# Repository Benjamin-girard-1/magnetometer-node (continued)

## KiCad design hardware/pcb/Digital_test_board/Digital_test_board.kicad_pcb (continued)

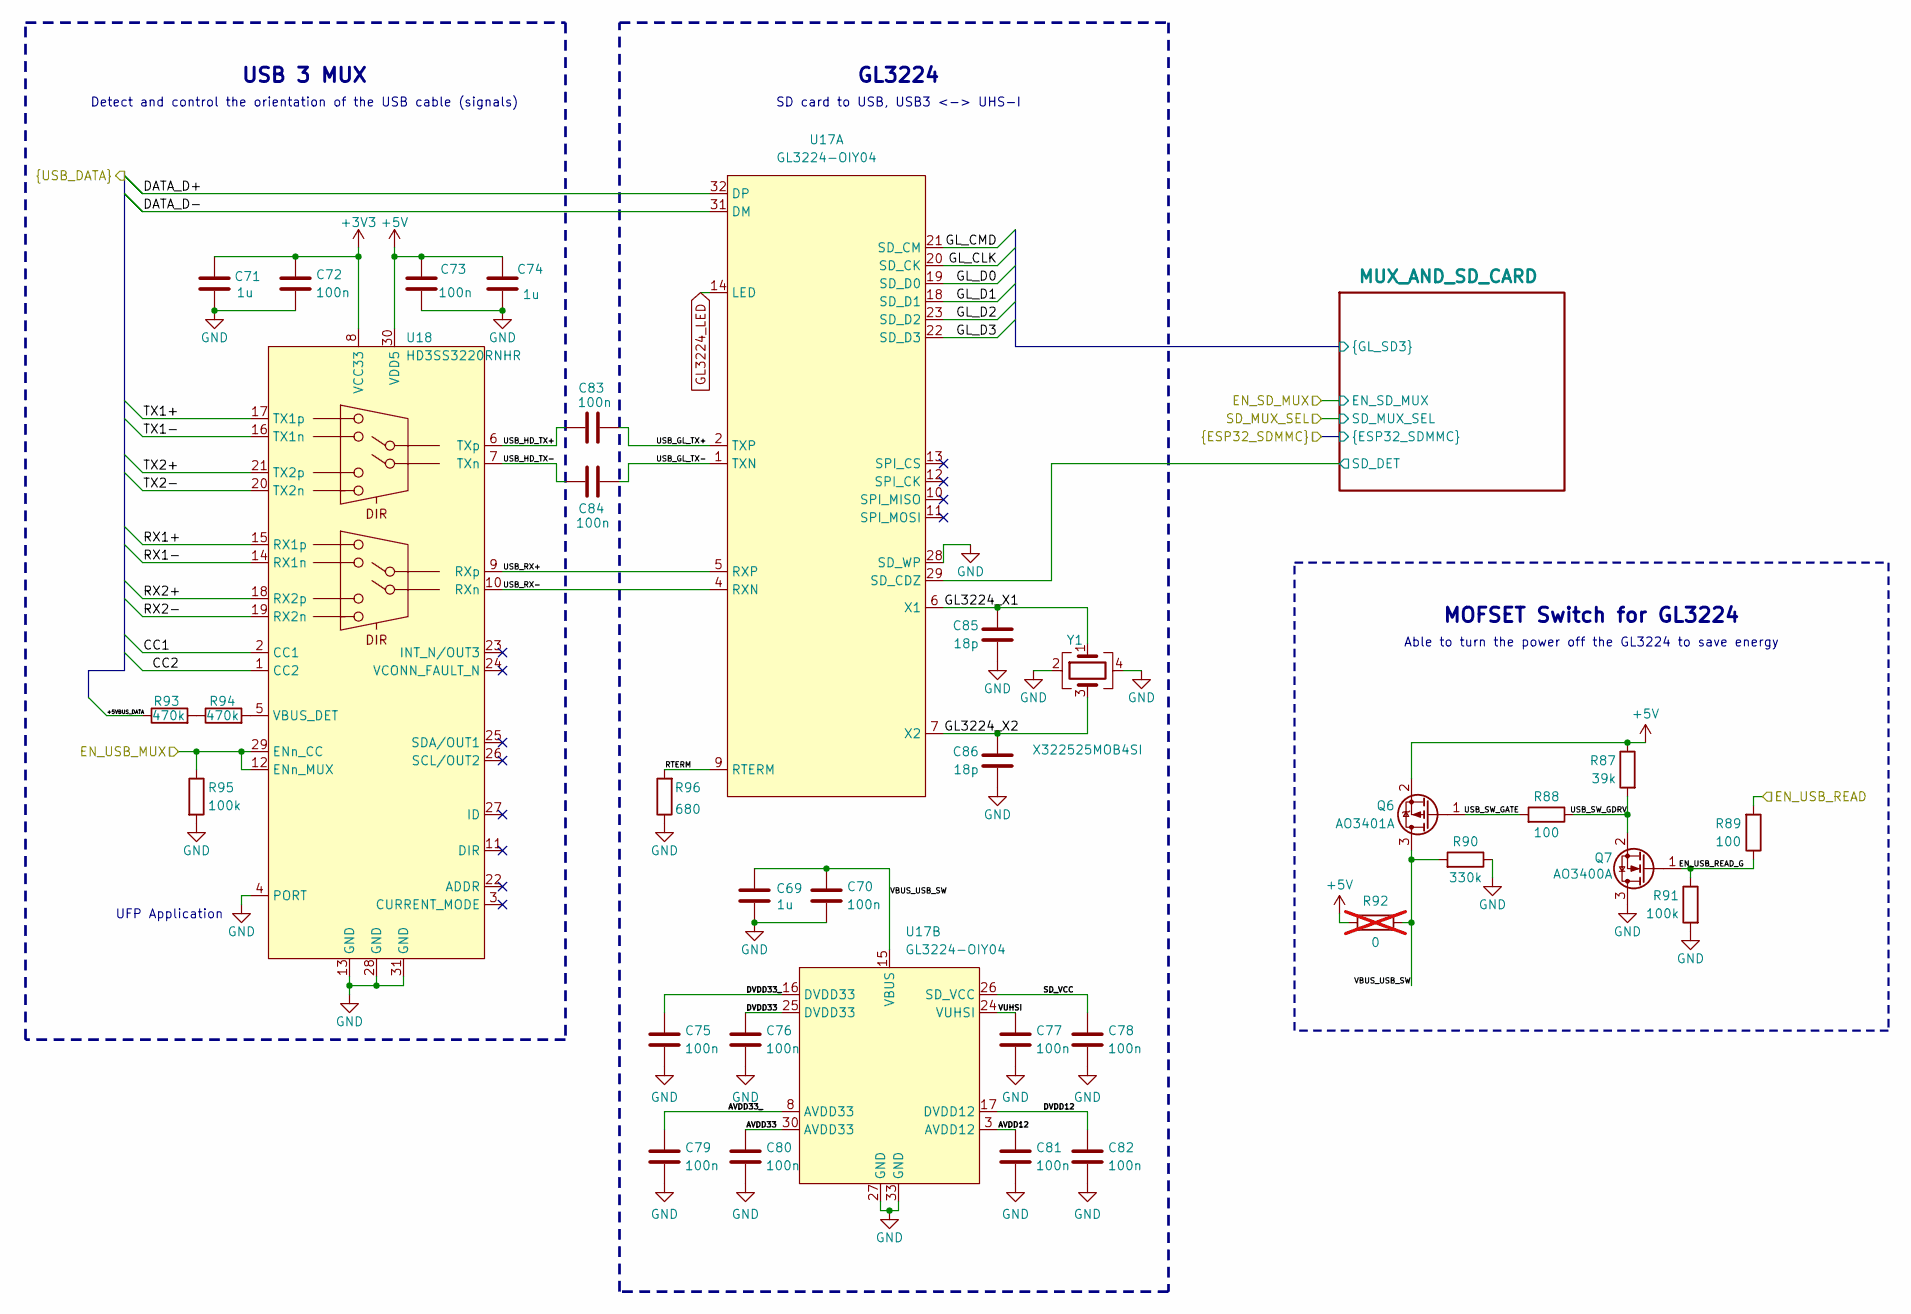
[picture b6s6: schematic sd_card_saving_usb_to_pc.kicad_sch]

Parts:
C69, C71, C74: 1u; C_0805_2012Metric; LCSC C28323
C70, C72, C73, C75, C76, C77, C78, C79, C80, C81, C82, C83, C84: 100n; C_0603_1608Metric; LCSC C14663
C85, C86: 18p; C_0603_1608Metric; LCSC C1647
Q6: AO3401A; SOT-23; LCSC C15127
Q7: AO3400A; SOT-23; LCSC C20917
R87: 39k; R_0603_1608Metric; LCSC C23153
R88, R89: 100; R_0603_1608Metric; LCSC C22775
R90: 330k; R_0603_1608Metric; LCSC C23137
R91, R95: 100k; R_0603_1608Metric; LCSC C25803
R92: 0; R_1206_3216Metric; LCSC C17888; not fitted
R93, R94: 470k; R_0603_1608Metric; LCSC C23178
R96: 680; R_0603_1608Metric; LCSC C23228
U17: GL3224-OIY04; QFN-32-1EP_5x5mm_P0.5mm_EP3.1x3.1mm; LCSC C157357
U18: HD3SS3220RNHR; Texas_RNH0030A_WQFN-30-1EP_2.5x4.5mm_P0.4mm_EP1.2x3.2mm; LCSC C165155
Y1: X322525MOB4SI; Crystal_SMD_3225-4Pin_3.2x2.5mm; LCSC C9006

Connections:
+3V3: C71.2, C72.1, U18.8 (VCC33); also elsewhere on the board
+5V: C73.1, C74.2, Q6.2 (S), R87.1, R92.2, U18.30 (VDD5); also elsewhere on the board
/DATA_SAVING/+5VBUS_DATA: R93.1; also elsewhere on the board
/DATA_SAVING/+5VBUS_DET: R94.2, U18.5 (VBUS_DET)
/DATA_SAVING/AVDD12: C81.1, U17.3 (AVDD12)
/DATA_SAVING/AVDD33: C80.1, U17.30 (AVDD33)
/DATA_SAVING/AVDD33_: C79.1, U17.8 (AVDD33)
/DATA_SAVING/CC1: U18.2 (CC1); also elsewhere on the board
/DATA_SAVING/CC2: U18.1 (CC2); also elsewhere on the board
/DATA_SAVING/DATA_D+: U17.32 (DP); also elsewhere on the board
/DATA_SAVING/DATA_D-: U17.31 (DM); also elsewhere on the board
/DATA_SAVING/DVDD12: C82.1, U17.17 (DVDD12)
/DATA_SAVING/DVDD33: C76.1, U17.25 (DVDD33)
/DATA_SAVING/DVDD33_: C75.1, U17.16 (DVDD33)
/DATA_SAVING/EN_USB_MUX: R95.1, U18.12 (ENn_MUX), U18.29 (ENn_CC); also elsewhere on the board
/DATA_SAVING/EN_USB_READ: R89.2; also elsewhere on the board
/DATA_SAVING/EN_USB_READ_G: Q7.1 (G), R89.1, R91.1
/DATA_SAVING/GL3224_X1: C85.1, U17.6 (X1), Y1.1
/DATA_SAVING/GL3224_X2: C86.1, U17.7 (X2), Y1.3
/DATA_SAVING/MUX_AND_SD_CARD/GL_CLK: U17.20 (SD_CK); also elsewhere on the board
/DATA_SAVING/MUX_AND_SD_CARD/GL_CMD: U17.21 (SD_CM); also elsewhere on the board
/DATA_SAVING/MUX_AND_SD_CARD/GL_D0: U17.19 (SD_D0); also elsewhere on the board
/DATA_SAVING/MUX_AND_SD_CARD/GL_D1: U17.18 (SD_D1); also elsewhere on the board
/DATA_SAVING/MUX_AND_SD_CARD/GL_D2: U17.23 (SD_D2); also elsewhere on the board
/DATA_SAVING/MUX_AND_SD_CARD/GL_D3: U17.22 (SD_D3); also elsewhere on the board
/DATA_SAVING/MUX_AND_SD_CARD/SD_DET: U17.29 (SD_CDZ); also elsewhere on the board
/DATA_SAVING/RTERM: R96.2, U17.9 (RTERM)
/DATA_SAVING/RX1+: U18.15 (RX1p); also elsewhere on the board
/DATA_SAVING/RX1-: U18.14 (RX1n); also elsewhere on the board
/DATA_SAVING/RX2+: U18.18 (RX2p); also elsewhere on the board
/DATA_SAVING/RX2-: U18.19 (RX2n); also elsewhere on the board
/DATA_SAVING/SD_VCC: C78.1, U17.26 (SD_VCC)
/DATA_SAVING/TX1+: U18.17 (TX1p); also elsewhere on the board
/DATA_SAVING/TX1-: U18.16 (TX1n); also elsewhere on the board
/DATA_SAVING/TX2+: U18.21 (TX2p); also elsewhere on the board
/DATA_SAVING/TX2-: U18.20 (TX2n); also elsewhere on the board
/DATA_SAVING/USB_GL_TX+: C83.2, U17.2 (TXP)
/DATA_SAVING/USB_GL_TX-: C84.2, U17.1 (TXN)
/DATA_SAVING/USB_HD_TX+: C83.1, U18.6 (TXp)
/DATA_SAVING/USB_HD_TX-: C84.1, U18.7 (TXn)
/DATA_SAVING/USB_RX+: U17.5 (RXP), U18.9 (RXp)
/DATA_SAVING/USB_RX-: U17.4 (RXN), U18.10 (RXn)
/DATA_SAVING/USB_SW_GATE: Q6.1 (G), R88.2
/DATA_SAVING/USB_SW_GDRV: Q7.2 (S), R87.2, R88.1
/DATA_SAVING/VBUS_USB_SW: C69.2, C70.1, Q6.3 (D), R90.2, R92.1, U17.15 (VBUS)
/DATA_SAVING/VUHSI: C77.1, U17.24 (VUHSI)
GL3224_LED: U17.14 (LED); also elsewhere on the board
GND: C69.1, C70.2, C71.1, C72.2, C73.2, C74.1, C75.2, C76.2, C77.2, C78.2, C79.2, C80.2, C81.2, C82.2, C85.2, C86.2, Q7.3 (D), R90.1, R91.2, R95.2, R96.1, U17.27 (GND), U17.28 (SD_WP), U17.33 (GND), U18.4 (PORT), U18.13 (GND), U18.28 (GND), U18.31 (GND), Y1.2, Y1.4; also elsewhere on the board
unnamed: R93.2, R94.1

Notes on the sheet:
USB 3 MUX
Detect and control the orientation of the USB cable (signals)
GL3224
UFP Application
MOFSET Switch for GL3224
Able to turn the power off the GL3224 to save energy
SD card to USB, USB3 <-> UHS-I

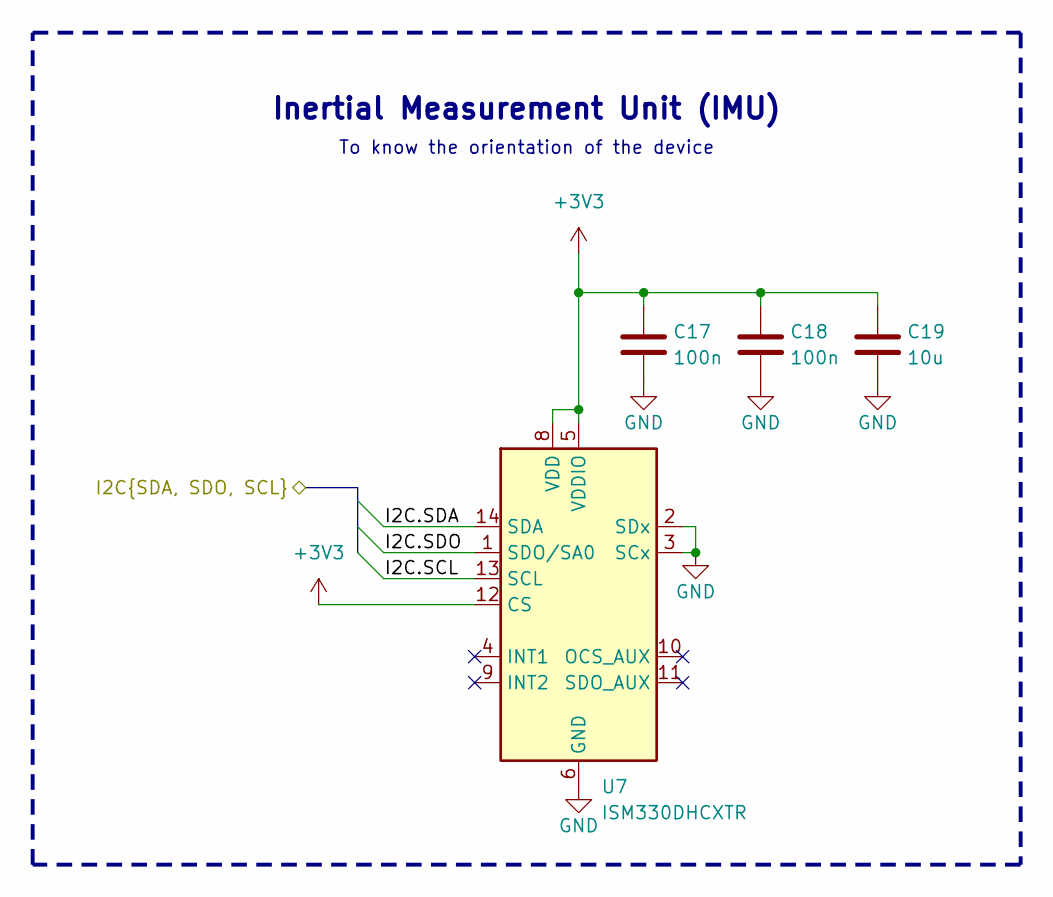
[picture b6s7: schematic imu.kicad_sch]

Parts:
C17, C18: 100n; C_0603_1608Metric; LCSC C14663
C19: 10u; C_0805_2012Metric; LCSC C15850
U7: ISM330DHCXTR; LGA-14_3x2.5mm_P0.5mm_LayoutBorder3x4y; LCSC C2655101

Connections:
+3V3: C17.1, C18.1, C19.1, U7.5 (VDDIO), U7.8 (VDD), U7.12 (CS); also elsewhere on the board
/IMU/I2C.SCL: U7.13 (SCL); also elsewhere on the board
/IMU/I2C.SDA: U7.14 (SDA); also elsewhere on the board
/IMU/I2C.SDO: U7.1 (SDO/SA0); also elsewhere on the board
GND: C17.2, C18.2, C19.2, U7.2 (SDx), U7.3 (SCx), U7.6 (GND), U7.7 (GND); also elsewhere on the board

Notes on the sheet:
Inertial Measurement Unit (IMU)
To know the orientation of the device

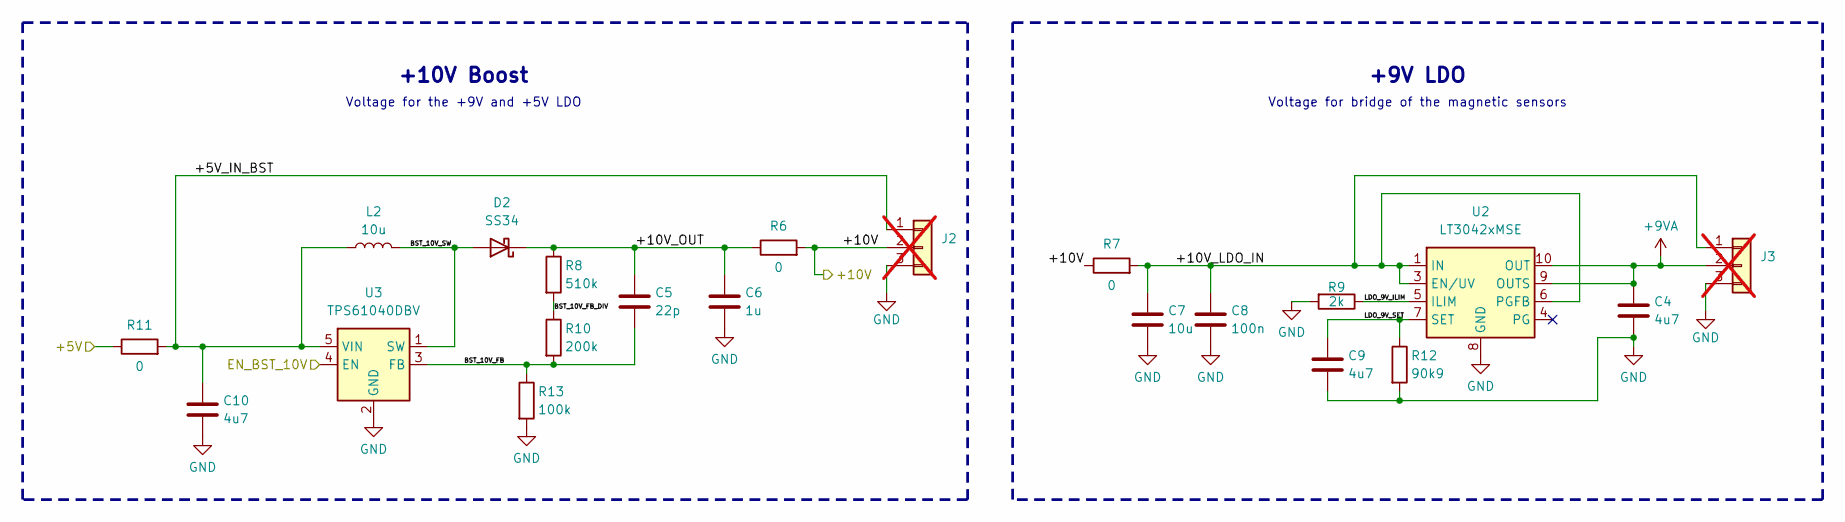
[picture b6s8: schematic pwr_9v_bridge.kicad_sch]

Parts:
C4, C9, C10: 4u7; C_1206_3216Metric; LCSC C29823
C5: 22p; C_0603_1608Metric; LCSC C1653
C6: 1u; C_0805_2012Metric; LCSC C28323
C7: 10u; C_0805_2012Metric; LCSC C15850
C8: 100n; C_0603_1608Metric; LCSC C14663
D2: SS34; D_SMA; LCSC C8678
J2, J3: Conn_01x03; PinHeader_1x03_P2.54mm_Vertical; not fitted
L2: 10u; L_Sunlord_MWSA0503S; LCSC C177248
R6, R7, R11: 0; R_1206_3216Metric; LCSC C17888
R8: 510k; R_0603_1608Metric; LCSC C23192
R9: 2k; R_0603_1608Metric; LCSC C22975
R10: 200k; R_0603_1608Metric; LCSC C25811
R12: 90k9; R_1206_3216Metric; LCSC C870933
R13: 100k; R_0603_1608Metric; LCSC C25803
U2: LT3042xMSE; MSOP-10-1EP_3x3mm_P0.5mm_EP1.68x1.88mm; LCSC C580009
U3: TPS61040DBV; SOT-23-5; LCSC C7722

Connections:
+5V: R11.1; also elsewhere on the board
+9VA: C4.1, J3.2, U2.9 (OUTS), U2.10 (OUT)
/MCU_ESP32S3/EN_BST_10V: U3.4 (EN); also elsewhere on the board
/PWR_9V_BRIDGE/+5V_IN_BST: C10.1, J2.1, L2.1, R11.2, U3.5 (VIN)
/PWR_9V_BRIDGE/+10V: J2.2, R6.2, R7.1; also elsewhere on the board
/PWR_9V_BRIDGE/+10V_LDO_IN: C7.1, C8.1, J3.1, R7.2, U2.1 (IN), U2.2 (IN), U2.3 (EN/UV), U2.6 (PGFB)
/PWR_9V_BRIDGE/+10V_OUT: C5.1, C6.1, D2.1 (K), R6.1, R8.1
/PWR_9V_BRIDGE/BST_10V_FB: C5.2, R10.2, R13.1, U3.3 (FB)
/PWR_9V_BRIDGE/BST_10V_FB_DIV: R8.2, R10.1
/PWR_9V_BRIDGE/BST_10V_SW: D2.2 (A), L2.2, U3.1 (SW)
/PWR_9V_BRIDGE/LDO_9V_ILIM: R9.1, U2.5 (ILIM)
/PWR_9V_BRIDGE/LDO_9V_SET: C9.1, R12.1, U2.7 (SET)
GND: C4.2, C6.2, C7.2, C8.2, C9.2, C10.2, J2.3, J3.3, R9.2, R12.2, R13.2, U2.8 (GND), U2.11 (GND), U3.2 (GND); also elsewhere on the board

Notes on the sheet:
Voltage for bridge of the magnetic sensors
+9V LDO
Voltage for the +9V and +5V LDO
+10V Boost

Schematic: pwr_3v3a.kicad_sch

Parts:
C46, C49: 4u7; C_1206_3216Metric; LCSC C29823
C47, C48: 100n; C_0603_1608Metric; LCSC C14663
FB1: FerriteBead; L_0603_1608Metric; LCSC C14709
J10: Conn_01x03; PinHeader_1x03_P2.54mm_Vertical; not fitted
R71, R72: 0; R_1206_3216Metric; LCSC C17888
U13: TPS7A2033PDBVR; SOT-23-5; LCSC C2862740

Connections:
+3V3A: J10.2, R72.2
+5V: R71.1; also elsewhere on the board
/MCU_ESP32S3/EN_LDO_3V3: U13.3 (EN); also elsewhere on the board
/PWR_3V3A/+5V_IN: FB1.1, J10.1, R71.2
/PWR_3V3A/LDO_3V3_IN: C46.1, C47.1, FB1.2, U13.1 (IN)
/PWR_3V3A/LDO_3V3_OUT: C48.1, C49.1, R72.1, U13.5 (OUT)
GND: C46.2, C47.2, C48.2, C49.2, J10.3, U13.2 (GND), U13.4 (NC); also elsewhere on the board

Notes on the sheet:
+3.3V LDO
Voltage for analog domain of the ADC

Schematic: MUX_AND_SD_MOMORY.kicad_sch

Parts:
C30, C32: 100n; C_0603_1608Metric; LCSC C14663
C31: 1u; C_0805_2012Metric; LCSC C28323
C33: 10u; C_0805_2012Metric; LCSC C15850
J6: Micro_SD_CARD; CONN_503398-1892_MOL; LCSC C428492
R44, R45: 100k; R_0603_1608Metric; LCSC C25803
R46, R47, R48, R49, R50, R51: 10k; R_0603_1608Metric; LCSC C25804
U10: TS3A27518ERTW; TSSOP-24_4.4x7.8mm_P0.65mm; LCSC C2651937

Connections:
+3V3: C30.1, C31.2, C32.1, C33.1, J6.4 (VDD), R44.1, R45.1, R46.1, R47.1, R48.1, R49.1, R50.1, R51.1, U10.5 (VCC); also elsewhere on the board
/DATA_SAVING/EN_SD_MUX: R45.2, U10.17 (~EN); also elsewhere on the board
/DATA_SAVING/E_CLK: R48.2, U10.12 (NO3); also elsewhere on the board
/DATA_SAVING/E_CMD: R49.2, U10.14 (NO4); also elsewhere on the board
/DATA_SAVING/E_D0: R47.2, U10.10 (NO2); also elsewhere on the board
/DATA_SAVING/E_D1: R46.2, U10.8 (NO1); also elsewhere on the board
/DATA_SAVING/E_D2: R51.2, U10.13 (NO6); also elsewhere on the board
/DATA_SAVING/E_D3: R50.2, U10.15 (NO5); also elsewhere on the board
/DATA_SAVING/MUX_AND_SD_CARD/GL_CLK: U10.20 (NC3); also elsewhere on the board
/DATA_SAVING/MUX_AND_SD_CARD/GL_CMD: U10.18 (NC4); also elsewhere on the board
/DATA_SAVING/MUX_AND_SD_CARD/GL_D0: U10.22 (NC2); also elsewhere on the board
/DATA_SAVING/MUX_AND_SD_CARD/GL_D1: U10.23 (NC1); also elsewhere on the board
/DATA_SAVING/MUX_AND_SD_CARD/GL_D2: U10.19 (NC6); also elsewhere on the board
/DATA_SAVING/MUX_AND_SD_CARD/GL_D3: U10.16 (NC5); also elsewhere on the board
/DATA_SAVING/MUX_AND_SD_CARD/MCLK: J6.5 (CLK), U10.4 (COM3)
/DATA_SAVING/MUX_AND_SD_CARD/MCMD: J6.3 (CMD), U10.6 (COM4)
/DATA_SAVING/MUX_AND_SD_CARD/MD0: J6.7 (DAT0), U10.3 (COM2)
/DATA_SAVING/MUX_AND_SD_CARD/MD1: J6.8 (DAT1), U10.1 (COM1)
/DATA_SAVING/MUX_AND_SD_CARD/MD2: J6.1 (DAT2), U10.9 (COM6)
/DATA_SAVING/MUX_AND_SD_CARD/MD3: J6.2 (DAT3), U10.7 (COM5)
/DATA_SAVING/MUX_AND_SD_CARD/SD_DET: J6.9 (DET); also elsewhere on the board
/DATA_SAVING/SD_MUX_SEL: R44.2, U10.11 (IN2), U10.21 (IN1); also elsewhere on the board
GND: C30.2, C31.1, C32.2, C33.2, J6.6 (VSS), J6.10 (SHIELD), J6.11 (VSS), J6.12 (VSS), J6.13 (VSS), J6.14 (VSS), U10.2 (GND); also elsewhere on the board

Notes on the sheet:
Expand the number of GPIO
Write with ESP32 / Read with GL3224
Shift register
SD Card MUX

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
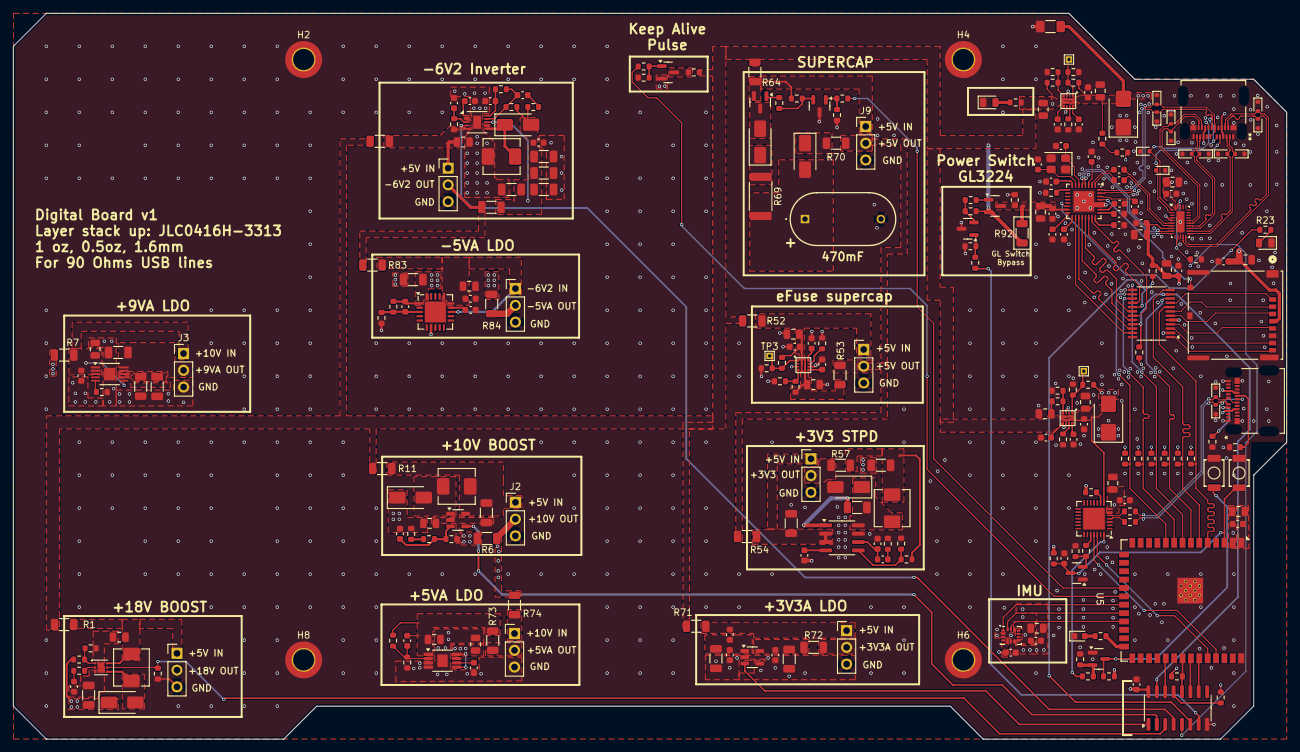
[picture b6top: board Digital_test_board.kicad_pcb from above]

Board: 4 copper layers, 193.0 x 110.0 mm, 260 parts (0 on the bottom side), 172 nets.

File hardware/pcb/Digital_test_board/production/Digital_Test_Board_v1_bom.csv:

Designator,Footprint,Quantity,Value,LCSC Part #
"C1, C12, C19, C22, C27, C33, C36, C50, C52, C57, C58, C7",0805,12,10u,C15850
"C10, C2, C4, C46, C49, C63, C64, C65, C66, C9",1206,10,4u7,C29823
"C11, C14, C15, C16, C17, C18, C21, C26, C30, C32, C35, C47, C48, C54, C59, C68, C70, C72, C73, C75, C76, C77, C78, C79, C8, C80, C81, C82, C83, C84",0603,30,100n,C14663
"C13, C20, C25, C31, C34, C6, C69, C71, C74",0805,9,1u,C28323
"C23, C28, C3, C42, C43, C51, C53, C60, C62",0603,9,10n,C57112
"C24, C29, C44",0603,3,1n,C1588
"C37, C38",1206,2,22u,C12891
"C39, C61",1206,2,47u,C96123
"C40, C67",0603,2,4n7,C53987
"C41, C56",0603,2,10p,C1634
C5,0603,1,22p,C1653
C55,0603,1,220n,C21120
"C85, C86",0603,2,18p,C1647
"D1, D2, D22, D23, D24, D25",D_SMA,6,SS34,C8678
"D10, D11, D12, D13, D14, D15, D16, D17, D18, D20, D21, D7, D8, D9",D_SOD-523,14,H5VUD5BB,C20615820
"D19, D6",D_SMB,2,P6SMB6.8CA,C7420377
D3,0805,1,KT-0805G,C2297
D4,0603,1,KT-0603W,C2290
D5,0805,1,NCD0805R1,C84256
FB1,0603,1,FerriteBead,C14709
"J4, J5",CONN_201267-0005_MOL,2,USB_C_RECEPTACLE_MOLEX,C565324
J6,CONN_503398-1892_MOL,1,Micro_SD_CARD,C428492
"L1, L2, L3, L4",L_Sunlord_MWSA0503S,4,10u,C177248
"Q1, Q2",SOT-23,2,S8050,C2146
"Q3, Q5, Q7",SOT-23,3,AO3400A,C20917
"Q4, Q6",SOT-23,2,AO3401A,C15127
"R1, R11, R52, R53, R54, R57, R6, R64, R7, R70, R71, R72, R73, R74, R79, R82, R83, R84",1206,18,0,C17888
"R10, R30, R36, R58",0603,4,200k,C25811
R12,1206,1,90k9,C870933
"R13, R26, R27, R29, R3, R35, R41, R44, R45, R56, R68, R77, R81, R86, R91, R95",0603,16,100k,C25803
"R14, R17, R18, R19, R20, R21, R24, R25, R4, R46, R47, R48, R49, R50, R51, R61",0603,16,10k,C25804
"R15, R16",0603,2,22,C23345
R2,0603,1,49k9,C23184
R22,0603,1,470,C23179
R23,0603,1,1k,C21190
"R28, R34, R55, R93, R94",0603,5,470k,C23178
"R31, R37, R59, R65, R75, R87",0603,6,39k,C23153
"R33, R38, R63, R9",0603,4,2k,C22975
"R39, R40, R66, R67, R88, R89",0603,6,100,C22775
"R42, R43",0603,2,5k1,C23186
R5,0603,1,3k6,C22980
R60,0603,1,75k,C23242
R62,0603,1,24k,C23352
R76,0603,1,12k,C22790
R78,0603,1,10,C22859
"R8, R80",0603,2,510k,C23192
"R85, R90",0603,2,330k,C23137
R96,0603,1,680,C23228
"SW1, SW2",TS-1088-AR02016,2,TS-1088-AR02016,C720477
U1,WSON-6-1EP_2x2mm_P0.65mm_EP1x1.6mm,1,TPS61170,C15163
U10,TSSOP-24_4.4x7.8mm_P0.65mm,1,TS3A27518EPWR,C443721
"U11, U8, U9",VQFN-HR-10,3,TPS25210LRPWR,C2861226
U12,SOIC-8_3.9x4.9mm_P1.27mm,1,TPS54331DR,C9865
U13,SOT-23-5,1,TPS7A2033PDBVR,C2862740
U14,HVSSOP-8-1EP_3x3mm_P0.65mm_EP1.57x1.89mm,1,TPS7A4901DGNR,C16430
U15,VSON-10-1EP_3x3mm_P0.5mm_EP1.2x2mm,1,TPS63700DRCR,C54792
U16,Texas_RGW0020A_VQFN-20-1EP_5x5mm_P0.65mm_EP3.15x3.15mm,1,TPS7A3301RGWR,C90082
U17,QFN-32-1EP_5x5mm_P0.5mm_EP3.1x3.1mm,1,GL3224-OIY04,C157357
U18,Texas_RNH0030A_WQFN-30-1EP_2.5x4.5mm_P0.4mm_EP1.2x3.2mm,1,HD3SS3220RNHR,C165155
U2,MSOP-10-1EP_3x3mm_P0.5mm_EP1.68x1.88mm,1,LT3042xMSE,C580009
U3,SOT-23-5,1,TPS61040DBV,C7722
U4,SOIC-16_3.9x9.9mm_P1.27mm,1,"74HC595D,118",C5947
U5,ESP32-S3-WROOM-1,1,ESP32-S3-WROOM-1,C2913202
U6,QFN-28-1EP_5x5mm_P0.5mm_EP3.25x3.25mm,1,CP2102-GMR,C6568
U7,LGA-14_3x2.5mm_P0.5mm_LayoutBorder3x4y,1,ISM330DHCXTR,C2655101
Y1,Crystal_SMD_3225-4Pin_3.2x2.5mm,1,X322525MOB4SI,C9006

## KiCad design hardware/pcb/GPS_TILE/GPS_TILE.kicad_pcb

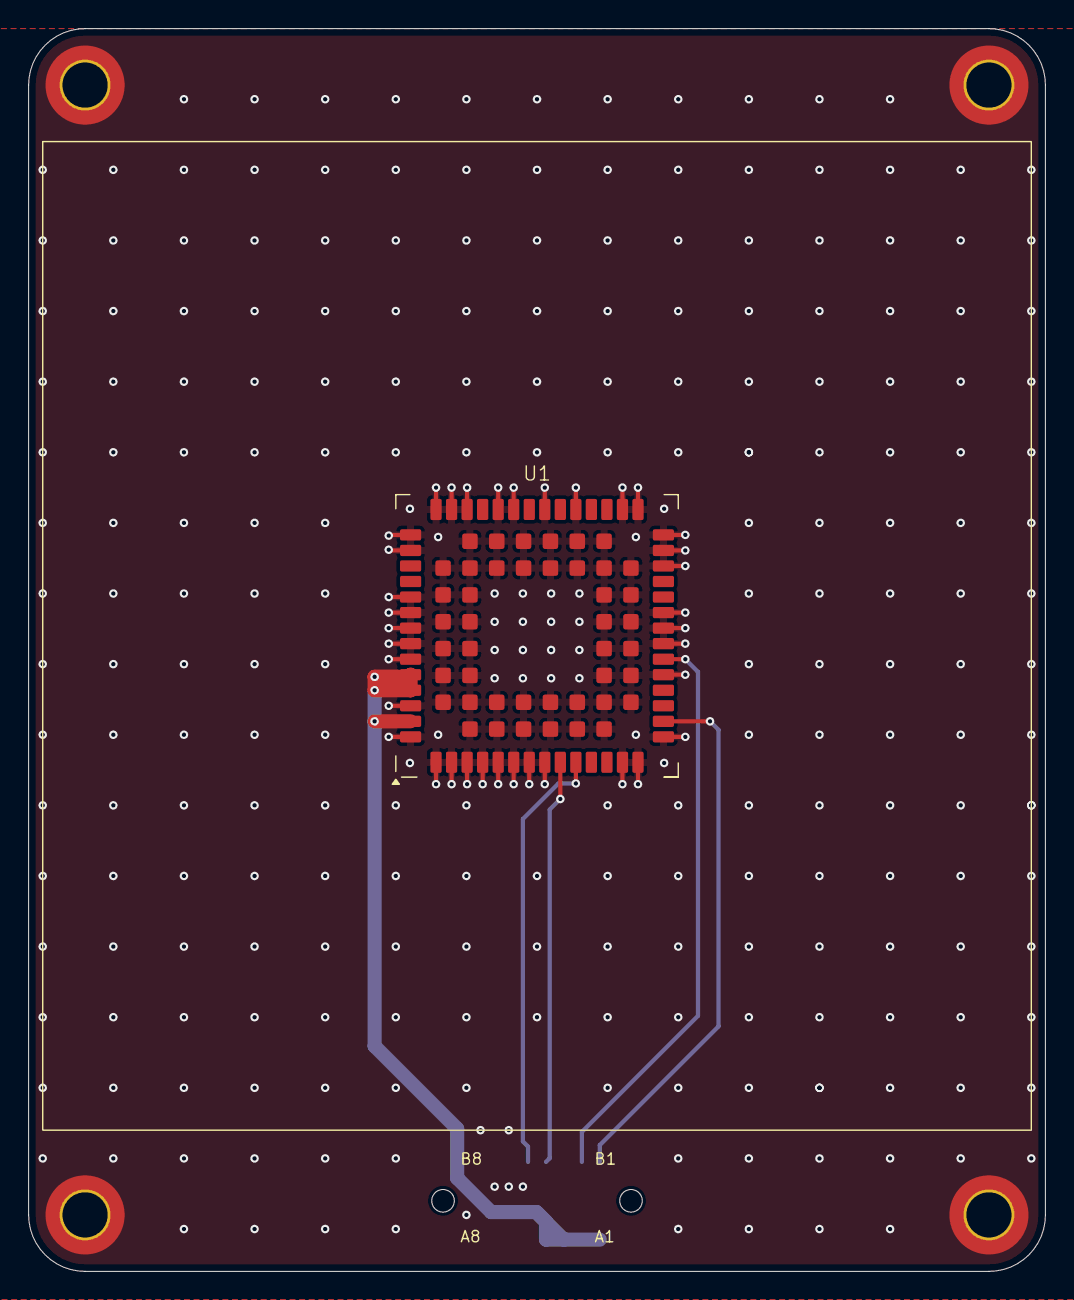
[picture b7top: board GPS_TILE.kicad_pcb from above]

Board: 2 copper layers, 72.0 x 88.0 mm, 6 parts (1 on the bottom side), 6 nets.

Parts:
H1, H2, H3, H4: MountingHole_Pad; MountingHole_3.2mm_M3_DIN965_Pad_TopBottom
J1: 1374028; PHOENIX_1374028
U1: DAN-F10N; u-blox_DAN-F10N_LCC-56_20x20mm

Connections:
+3.3V: J1.A1, J1.A2, J1.A3, J1.A4, U1.52 (VCC), U1.53 (VCC), U1.55 (V_BCKP)
/GPS_NRESET: J1.B1, U1.16 (RESET_N)
/GPS_TIMEPULSE: J1.B2, U1.20 (TIMEPULSE)
/GPS_UART.RX: J1.B4, U1.9 (RXD)
/GPS_UART.TX: J1.B5, U1.10 (TXD)
GND: H1.1, H2.1, H3.1, H4.1, J1.A5, J1.A6, J1.A7, J1.A8, J1.B6, J1.B7, J1.B8, J1.MP1, J1.MP2, J1.MP3, J1.MP4, U1.1 (GND), U1.2 (GND), U1.3 (GND), U1.4 (GND), U1.5 (GND), U1.6 (GND), U1.7 (GND), U1.8 (GND), U1.13 (GND), U1.14 (GND), U1.15 (GND), U1.19 (GND), U1.21 (GND), U1.22 (GND), U1.23 (GND), U1.26 (GND), U1.27 (GND), U1.28 (GND), U1.29 (GND), U1.30 (GND), U1.33 (GND), U1.35 (GND), U1.37 (GND), U1.38 (GND), U1.40 (GND), U1.41 (GND), U1.42 (GND), U1.43 (GND), U1.44 (GND), U1.47 (GND), U1.48 (GND), U1.49 (GND), U1.50 (GND), U1.51 (GND), U1.54 (GND), U1.56 (GND), U1.EP
